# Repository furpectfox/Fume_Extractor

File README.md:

# Fume Extractor
This Solder Fume Extractor features a 12V Noctua fan, with speed controlled by a PWM signal generated by a Colpitts sinusoidal oscillator circuit. The frequency generated is close to 25kHz, which is required by the Noctua fan. It also includes an LED strip to illuminate the workspace, with its brightness similarly controlled via PWM for greater efficiency. Since the supply voltage is 12V, using a linear regulator is inefficient and would create a lot of heat.

***Note***: Although this project could be greatly simplified by incorporating a microcontroller, like an ATtiny or ATmega, to generate the PWM signals for both the fan and LED strip, the aim here is to explore how to generate a square wave with a controllable duty cycle using entirely analog components.

## [Schematic](KiCad/Schematic.pdf)

## PCB

## 3D Model

## Finish

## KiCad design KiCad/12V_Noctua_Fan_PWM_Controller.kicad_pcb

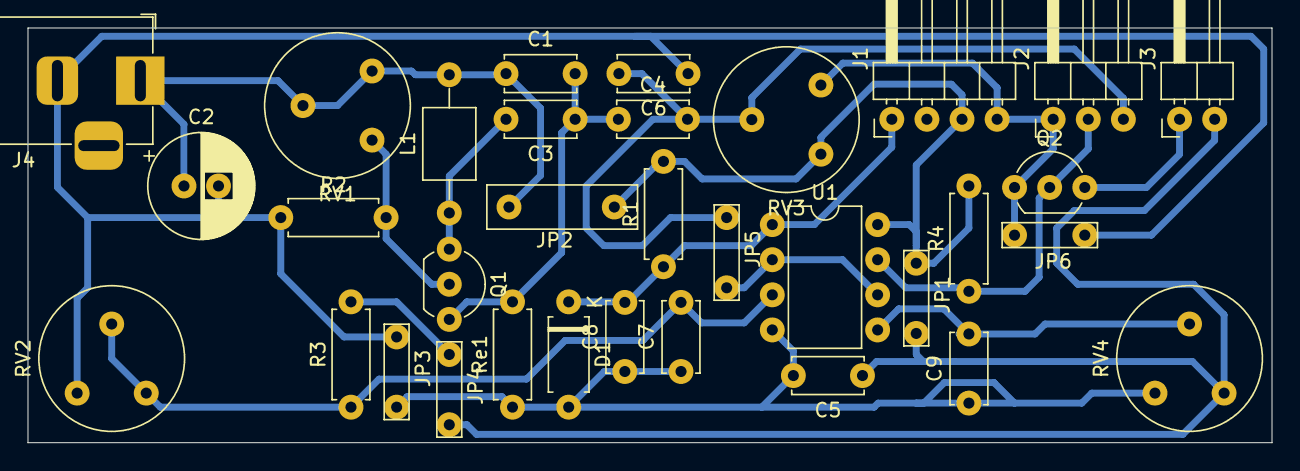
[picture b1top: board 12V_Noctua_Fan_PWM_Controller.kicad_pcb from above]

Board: 2 copper layers, 90.0 x 30.0 mm, 33 parts (0 on the bottom side), 11 nets.

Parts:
C1, C3, C4: 0.01uF; C_Disc_D5.0mm_W2.5mm_P5.00mm
C2: 680uF; CP_Radial_D7.5mm_P2.50mm
C5: 10uF; C_Disc_D5.0mm_W2.5mm_P5.00mm
C6: 100pF; C_Disc_D5.0mm_W2.5mm_P5.00mm
C7, C9: 1uF; C_Disc_D5.0mm_W2.5mm_P5.00mm
C8: 68pF; C_Disc_D5.0mm_W2.5mm_P5.00mm
D1: 5.1V; D_A-405_P7.62mm_Horizontal
J1: Conn_01x04_Pin; PinHeader_1x04_P2.54mm_Horizontal
J2: Conn_01x03_Pin; PinHeader_1x03_P2.54mm_Horizontal
J3: Conn_01x02_Pin; PinHeader_1x02_P2.54mm_Horizontal
J4: Barrel_Jack_MountingPin; BarrelJack_Horizontal
JP1, JP3, JP4, JP5, JP6: Jumper_2_Bridged; TestPoint_Bridge_Pitch5.08mm_Drill0.7mm
JP2: Jumper_2_Bridged; TestPoint_Bridge_Pitch7.62mm_Drill1.3mm
L1: 10mH; L_Axial_L5.0mm_D3.6mm_P10.00mm_Horizontal_Murata_BL01RN1A2A2
Q1: BC547; TO-92_Inline_Wide
Q2: 2N7000; TO-92_Inline_Wide
R1, R4: 1K; R_Axial_DIN0207_L6.3mm_D2.5mm_P7.62mm_Horizontal
R2, R3: 10K; R_Axial_DIN0207_L6.3mm_D2.5mm_P7.62mm_Horizontal
RV1, RV2, RV3: 10K; Potentiometer_Piher_PT-10-V05_Vertical
RV4: 5K; Potentiometer_Piher_PT-10-V05_Vertical
Re1: 10K; R_Axial_DIN0207_L6.3mm_D2.5mm_P7.62mm_Horizontal
U1: LM393; DIP-8_W7.62mm

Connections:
+12V: C1.1, C2.1, C5.1, J1.3, J3.2, J4.1, JP1.1 (A), JP2.1 (A), JP4.1 (A), L1.2, R1.2, R3.2, R4.2, RV1.1, RV1.2, RV3.3, RV4.1, U1.8 (V+)
/PWM_fan: C8.2, D1.1 (K), J1.1, R1.1, U1.1
/PWM_led: J2.2, Q2.2 (G), R4.1, U1.7
/drain_pin: J3.1, Q2.3 (D)
/osc_out: C4.2, C6.2, J2.3, JP5.1 (A), RV3.2, U1.2 (-), U1.6 (-)
GND: C2.2, C5.2, C6.1, C7.1, C8.1, C9.1, D1.2 (A), J1.4, J2.1, J4.2, JP3.1 (A), JP6.1 (A), Q2.1 (S), R2.1, RV2.3, RV3.1, RV4.3, Re1.1, U1.4 (V-)
unnamed: Q1.2 (B), R2.2, RV1.3
unnamed: C3.2, L1.1, Q1.1 (C)
unnamed: C1.2, C3.1, C4.1, Q1.3 (E), Re1.2
unnamed: C7.2, R3.1, RV2.1, RV2.2, U1.3 (+)
unnamed: C9.2, RV4.2, U1.5 (+)

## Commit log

2025-02-28 first comit
2025-02-28 add CAD Model of Fume Extractor
2025-03-11 Organize files
